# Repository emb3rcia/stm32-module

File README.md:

# stm32-module
Hello! This is my first MCU devboard, made for HackClub's Blueprint program. It features 66 goldpins, USB-C (USB-FS standard) port for data AND power, integrated 3.3V and 1.8V LDO and ESD protection on VBUS, DATA channels and CC channels! It uses 4 layer pcb (Front and Back are for power, IN1 and IN2 for GPIO connection). It uses STM32H7 64-LQFP Package MCU on it! I made it so I can have some devboard on hand as one-for-all. This is why theres so much power in this thing (384MHz!!!) and this many GPIO ports, and also why this has 1.8V LDO. You use it like any other devboard, **but note that it probably wont fit on breadboard, as it doesnt have the required distance present between connectors**

## Why i made it?

I thought it will be good learning project as well as giving me access to prototyping with mcu before commiting to making pcb. And i was right!

## What i learned:

Mainly how to deal with tight connection layout on PCB near MCU

# Images
Schematic v1 (old)

Schematic v1.5 (new, work in progress)

Schematic v2 (new)

PCB v1 (old, view via kicanvas so low quality screenshot, sorry)

PCB v2 (new)

3D (new)

# Q&A (no one said that but I want to include that lol)
> Traces look ugly

It is my second completed project overall. Also they weren't like high speed eg pcie so I just connected them as well as I can! I will try to make them nicer before production, but no promises. EDIT: Tried to make them nicer when rerouting everything, it worked like you can see.

# BOM
|Item                                     |Description                 |Needed|Ordered|Why more/less?                   |Unit Price ($)|Total Price ($) |URL                                              |
|-----------------------------------------|----------------------------|------|-------|---------------------------------|--------------|----------------|-------------------------------------------------|
|ST STM32H7B0RBT6                         |MCU                         |1     |1      |-                                |10.08$        |10.08$          |https://www.lcsc.com/product-detail/C730226.html |
|SEMTECH RCLAMP0502BATCT                  |CC and DATA lines esd       |2     |5      |5 is minimal order amount        |0.24$         |1.21$           |https://www.lcsc.com/product-detail/C117553.html |
|Littelfuse SMA6L5.0A                     |VBUS line esd               |1     |1      |-                                |0.79$         |0.79$           |https://www.lcsc.com/product-detail/C1974860.html|
|BL BL8072CLTR33                          |3.3V LDO                    |1     |5      |5 is minimal order amount        |0.19$         |0.97$           |https://www.lcsc.com/product-detail/C843780.html |
|TI TPS73618QDCQRQ1                       |1.8V LDO                    |1     |1      |-                                |1.54$         |1.54$           |https://www.lcsc.com/product-detail/C2877946.html|
|muRata GRM188Z71C475KE21D                |4.7uF capacitor             |1     |10     |10 is minimal order amount       |0.07$         |0.68$           |https://www.lcsc.com/product-detail/C389010.html |
|Samsung Electro-Mechanics CL10A105KA8NNNC|1uF capacitor               |2     |0      |I have 48 left from other project|-             |-               |https://www.lcsc.com/product-detail/C5673.html   |
|VISHAY VJ0603Y104JXQCW1BC                |100nF decap capacitor       |7     |10     |sold in increments of 5          |0.08$         |0.81$           |https://www.lcsc.com/product-detail/C3834925.html|
|Samsung Electro-Mechanics CL10A225KO8NNNC|2.2uF capacitor             |2     |50     |50 is minimal order amount       |0.0062$       |0.31$           |https://www.lcsc.com/product-detail/C23630.html  |
|UNI-ROYAL 0603WAF5101T5E                 |5.1kOhm 0.1w CC resistor    |2     |100    |100 is minimal order amount      |0.0012$       |0.12$           |https://www.lcsc.com/product-detail/C23186.html  |
|VISHAY CRCW060310K0DHEAP                 |10kOhm pull-up/down resistor|2     |5      |5 is minimal order amount        |0.12$         |0.58$           |https://www.lcsc.com/product-detail/C3917708.html|
|SHOU HAN TS6643TP 250gf 009              |BOOT and NRST button        |2     |50     |50 is minimal order amount       |0.0167$       |0.84$           |https://www.lcsc.com/product-detail/C5342967.html|
|SHOU HAN TYPE-C 16PIN 2MD(073)           |USB-C plug                  |1     |20     |20 is minimal order amount       |0.06$         |1.26$           |https://www.lcsc.com/product-detail/C2765186.html|
|PCB                                      |PCB                         |1     |5      |5 is minimal order amount        |-             |7$+1.5$ delivery|https://jlcpcb.com/                              |

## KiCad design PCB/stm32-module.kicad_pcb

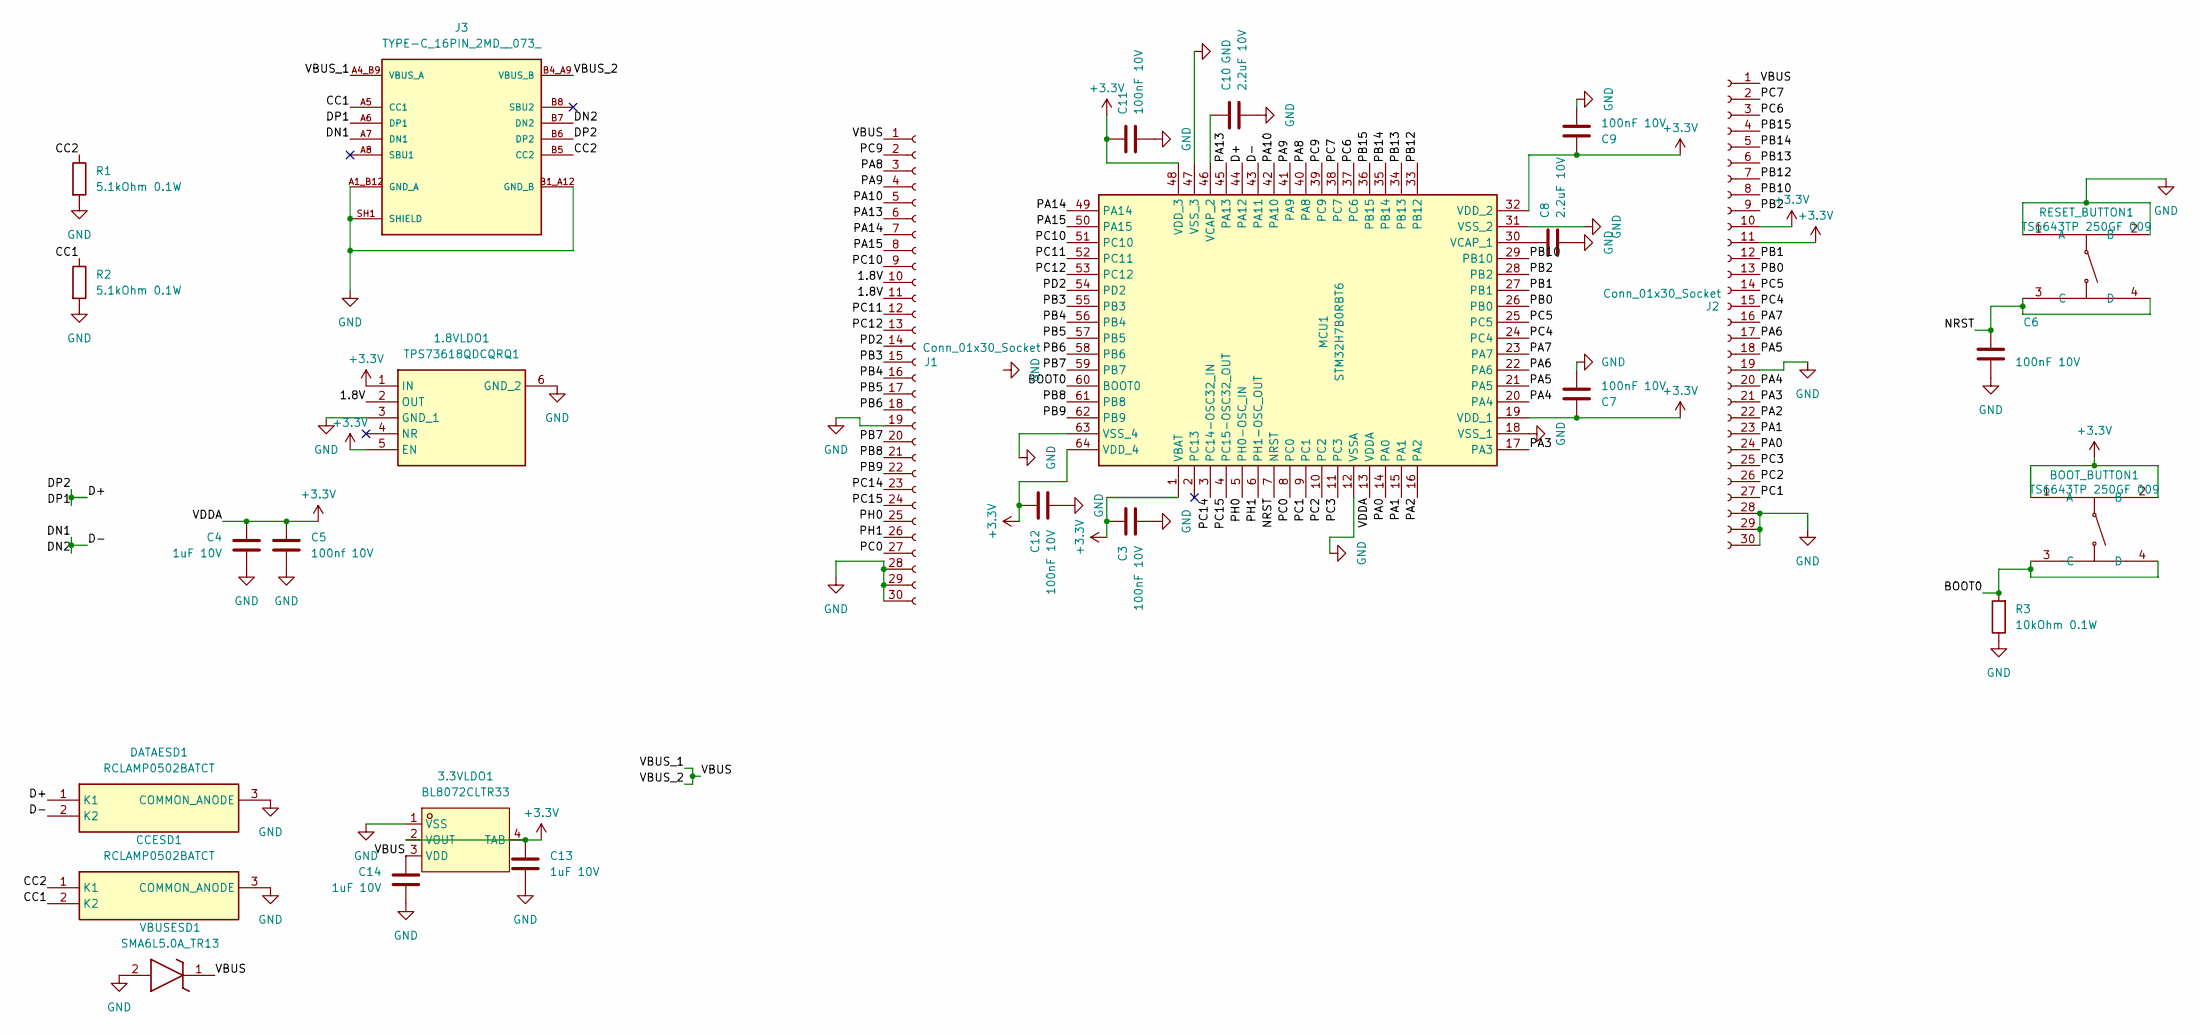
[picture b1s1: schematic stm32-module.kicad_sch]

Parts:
1.8VLDO1: TPS73618QDCQRQ1; SOT127P706X180-6N; Manufacturer_Part_Number TPS73618QDCQRQ1; Mouser Part Number 595-TPS73618QDCQRQ1
3.3VLDO1: BL8072CLTR33; SOT-223-3_L6.5-W3.4-P2.30-LS7.0-BR; LCSC Part C843780
BOOT_BUTTON1: TS6643TP 250GF 009; SW-SMD_4P-L6.2-W6.0-P4.50-LS9.0; LCSC Part C5342967
C3, C6, C7, C9, C11, C12: 100nF 10V; C_0603_1608Metric_Pad1.08x0.95mm_HandSolder
C4, C13, C14: 1uF 10V; C_0603_1608Metric_Pad1.08x0.95mm_HandSolder
C5: 100nf 10V; C_0603_1608Metric_Pad1.08x0.95mm_HandSolder
C8, C10: 2.2uF 10V; C_0603_1608Metric_Pad1.08x0.95mm_HandSolder
CCESD1: RCLAMP0502BATCT; SOT50P160X90-3N; Manufacturer_Part_Number RCLAMP0502BATCT; Mouser Part Number 947-RCLAMP0502BATCT
DATAESD1: RCLAMP0502BATCT; SOT50P160X90-3N; Manufacturer_Part_Number RCLAMP0502BATCT; Mouser Part Number 947-RCLAMP0502BATCT
J1, J2: Conn_01x30_Socket; PinSocket_1x30_P2.54mm_Vertical
J3: TYPE-C_16PIN_2MD__073_; SHOUHAN_TYPE-C_16PIN_2MD__073_; PARTREV A
MCU1: STM32H7B0RBT6; QFP50P1200X1200X160-64N; Manufacturer_Part_Number STM32H7B0RBT6; Mouser Part Number 511-STM32H7B0RBT6
R1, R2: 5.1kOhm 0.1W; R_0603_1608Metric_Pad0.98x0.95mm_HandSolder
R3: 10kOhm 0.1W; R_0603_1608Metric_Pad0.98x0.95mm_HandSolder
RESET_BUTTON1: TS6643TP 250GF 009; SW-SMD_4P-L6.2-W6.0-P4.50-LS9.0; LCSC Part C5342967
VBUSESD1: SMA6L5.0A_TR13; SODFL4626X140N; Manufacturer_Part_Number SMA6L5.0A/TR13

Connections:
+3.3V: 1.8VLDO1.1 (IN), 1.8VLDO1.5 (EN), 3.3VLDO1.2 (VOUT), 3.3VLDO1.4 (TAB), BOOT_BUTTON1.1 (A), BOOT_BUTTON1.2 (B), C3.1, C4.1, C5.1, C7.1, C9.1, C11.1, C12.1, C13.1, J2.10, J2.11, MCU1.1 (VBAT), MCU1.13 (VDDA), MCU1.19 (VDD_1), MCU1.32 (VDD_2), MCU1.48 (VDD_3), MCU1.64 (VDD_4)
/1.8V: 1.8VLDO1.2 (OUT), J1.10, J1.11
/BOOT0: BOOT_BUTTON1.3 (C), BOOT_BUTTON1.4 (D), MCU1.60 (BOOT0), R3.2
/CC1: CCESD1.2 (K2), J3.A5 (CC1), R2.1
/CC2: CCESD1.1 (K1), J3.B5 (CC2), R1.1
/D+: DATAESD1.1 (K1), J3.A6 (DP1), J3.B6 (DP2), MCU1.44 (PA12)
/D-: DATAESD1.2 (K2), J3.A7 (DN1), J3.B7 (DN2), MCU1.43 (PA11)
/NRST: C6.1, MCU1.7 (NRST), RESET_BUTTON1.3 (C), RESET_BUTTON1.4 (D)
/PA0: J2.24, MCU1.14 (PA0)
/PA1: J2.23, MCU1.15 (PA1)
/PA2: J2.22, MCU1.16 (PA2)
/PA3: J2.21, MCU1.17 (PA3)
/PA4: J2.20, MCU1.20 (PA4)
/PA5: J2.18, MCU1.21 (PA5)
/PA6: J2.17, MCU1.22 (PA6)
/PA7: J2.16, MCU1.23 (PA7)
/PA8: J1.3, MCU1.40 (PA8)
/PA9: J1.4, MCU1.41 (PA9)
/PA10: J1.5, MCU1.42 (PA10)
/PA13: J1.6, MCU1.45 (PA13)
/PA14: J1.7, MCU1.49 (PA14)
/PA15: J1.8, MCU1.50 (PA15)
/PB0: J2.13, MCU1.26 (PB0)
/PB1: J2.12, MCU1.27 (PB1)
/PB2: J2.9, MCU1.28 (PB2)
/PB3: J1.15, MCU1.55 (PB3)
/PB4: J1.16, MCU1.56 (PB4)
/PB5: J1.17, MCU1.57 (PB5)
/PB6: J1.18, MCU1.58 (PB6)
/PB7: J1.20, MCU1.59 (PB7)
/PB8: J1.21, MCU1.61 (PB8)
/PB9: J1.22, MCU1.62 (PB9)
/PB10: J2.8, MCU1.29 (PB10)
/PB12: J2.7, MCU1.33 (PB12)
/PB13: J2.6, MCU1.34 (PB13)
/PB14: J2.5, MCU1.35 (PB14)
/PB15: J2.4, MCU1.36 (PB15)
/PC0: J1.27, MCU1.8 (PC0)
/PC1: J2.27, MCU1.9 (PC1)
/PC2: J2.26, MCU1.10 (PC2)
/PC3: J2.25, MCU1.11 (PC3)
/PC4: J2.15, MCU1.24 (PC4)
/PC5: J2.14, MCU1.25 (PC5)
/PC6: J2.3, MCU1.37 (PC6)
/PC7: J2.2, MCU1.38 (PC7)
/PC9: J1.2, MCU1.39 (PC9)
/PC10: J1.9, MCU1.51 (PC10)
/PC11: J1.12, MCU1.52 (PC11)
/PC12: J1.13, MCU1.53 (PC12)
/PC14: J1.23, MCU1.3 (PC14-OSC32_IN)
/PC15: J1.24, MCU1.4 (PC15-OSC32_OUT)
/PD2: J1.14, MCU1.54 (PD2)
/PH0: J1.25, MCU1.5 (PH0-OSC_IN)
/PH1: J1.26, MCU1.6 (PH1-OSC_OUT)
/VBUS: 3.3VLDO1.3 (VDD), C14.1, J1.1, J2.1, J3.A4_B9 (VBUS_A), J3.B4_A9 (VBUS_B), VBUSESD1.1 (K)
GND: 1.8VLDO1.3 (GND_1), 1.8VLDO1.6 (GND_2), 3.3VLDO1.1 (VSS), C3.2, C4.2, C5.2, C6.2, C7.2, C8.2, C9.2, C10.2, C11.2, C12.2, C13.2, C14.2, CCESD1.3 (COMMON_ANODE), DATAESD1.3 (COMMON_ANODE), J1.19, J1.28, J1.29, J1.30, J2.19, J2.28, J2.29, J2.30, J3.A1_B12 (GND_A), J3.B1_A12 (GND_B), J3.SH1 (SHIELD), J3.SH2 (SHIELD), J3.SH3 (SHIELD), J3.SH4 (SHIELD), MCU1.12 (VSSA), MCU1.18 (VSS_1), MCU1.31 (VSS_2), MCU1.47 (VSS_3), MCU1.63 (VSS_4), R1.2, R2.2, R3.1, RESET_BUTTON1.1 (A), RESET_BUTTON1.2 (B), VBUSESD1.2 (A)
unnamed: C8.1, MCU1.30 (VCAP_1)
unnamed: C10.1, MCU1.46 (VCAP_2)

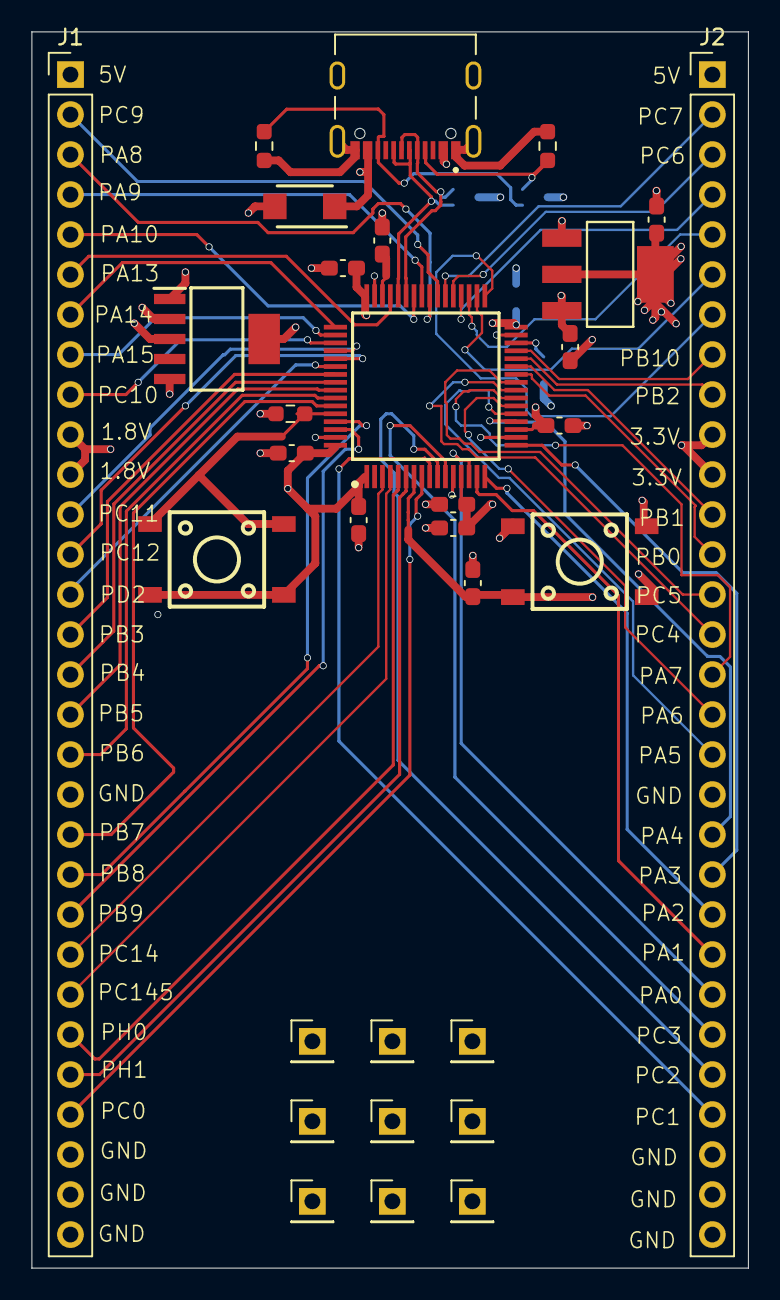
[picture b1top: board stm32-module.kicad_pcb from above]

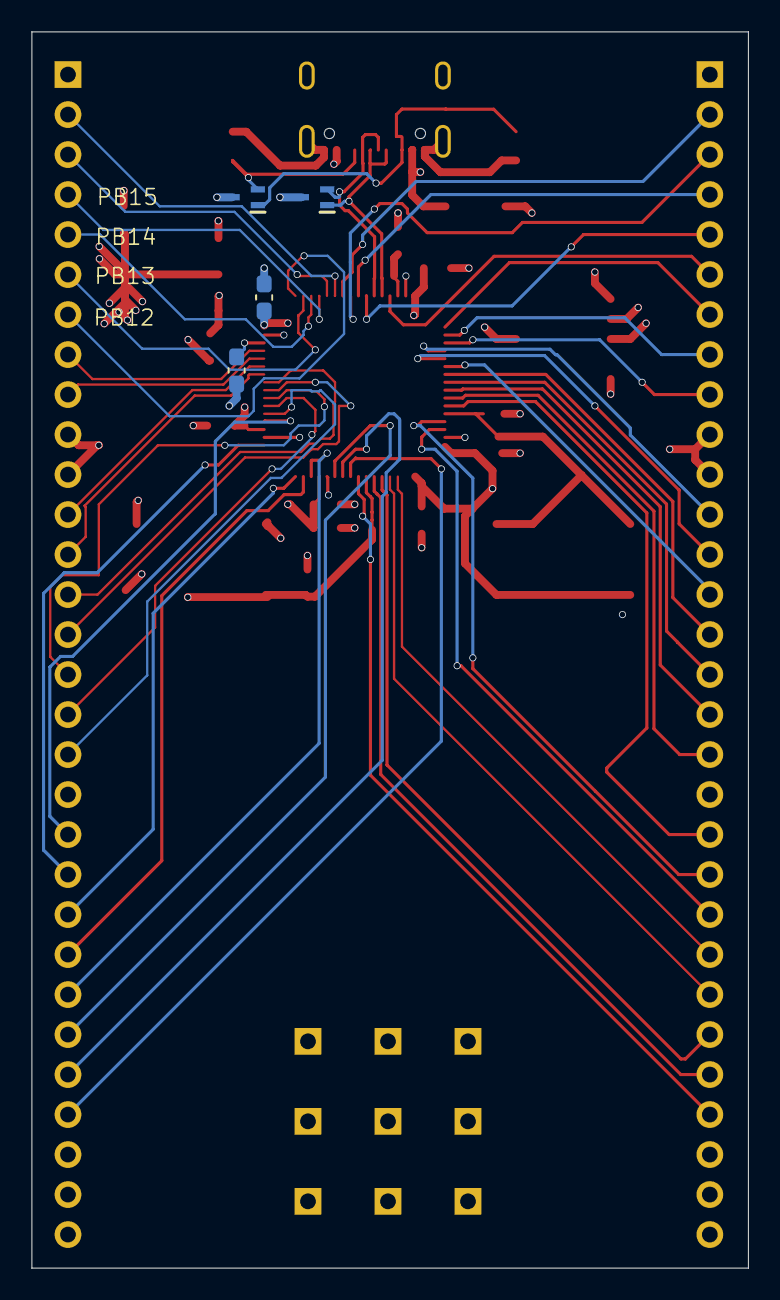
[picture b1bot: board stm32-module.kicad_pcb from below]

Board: 4 copper layers, 45.5 x 78.5 mm, 26 parts (4 on the bottom side), 58 nets.

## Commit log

2026-01-30 Added README.md
2026-01-30 Update README.md
    Added datasheet section
2026-01-30 Update README
    Added a section for datasheets
2026-01-30 Clean up README by removing project details
    Removed initial project description and part list from README.
2026-01-30 Added README.md content and more datasheets
2026-01-30 push
2026-01-30 Added images to rom, also rerouted everything
2026-01-31 Changed readme to reflect different switch chosen due to availability
2026-01-31 Changed readme, pcb and schematic to reflect different connector chosen due to availability
2026-01-31 Added bom to bom.csv and readme.md
2026-02-01 Added connector footprint with 3d model
2026-02-01 Added hat pins
2026-02-04 Corrected button wiring
2026-02-14 Added the purpose of creation of this project
2026-02-19 Changed README.md
2026-02-21 Updated bom
2026-03-16 delay tuned usb pair
2026-03-16 Delay tuned USB traces
2026-03-17 updated gerbers
2026-03-18 updated bom to reflect vbus change
2026-03-18 updated bom to reflect resistor change
2026-04-02 Changed ldo due to availability
2026-04-02 changed images to reflect changes
